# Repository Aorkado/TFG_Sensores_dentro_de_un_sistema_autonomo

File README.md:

# Sensores dentro de un sistema autónomo

En este repositorio se recoge el software desarrollado y las placas diseñadas. Varios ejemplos quedan por desarrollar o explicar debidamente. El proyecto aún está en progreso.

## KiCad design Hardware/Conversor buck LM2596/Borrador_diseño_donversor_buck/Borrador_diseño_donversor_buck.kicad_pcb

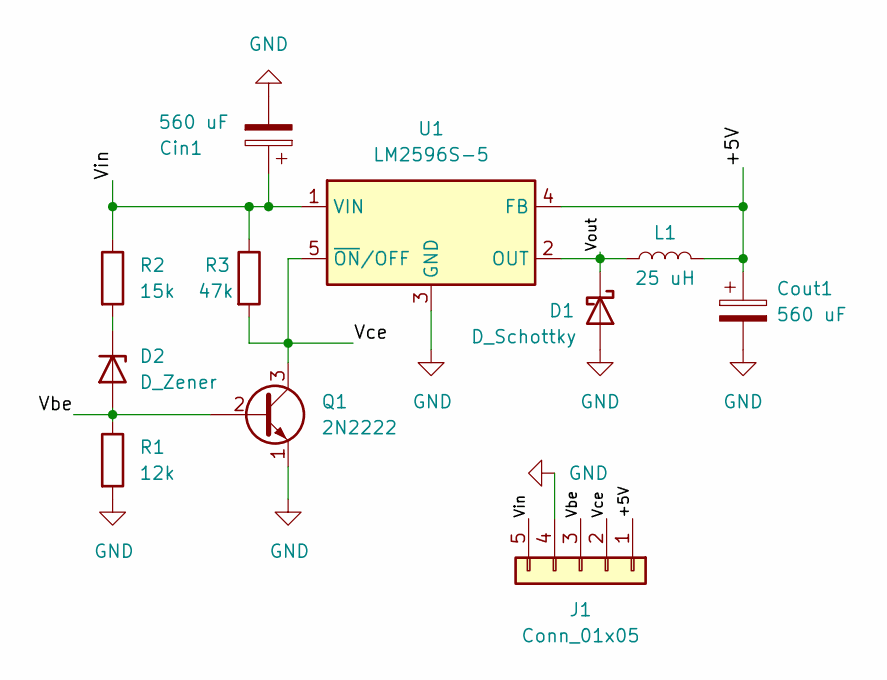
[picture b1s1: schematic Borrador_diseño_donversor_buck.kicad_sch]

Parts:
Cin1: 560 uF; CP_Radial_D8.0mm_P3.80mm
Cout1: 560 uF; CP_Radial_D8.0mm_P3.80mm
D1: D_Schottky; D_DO-201AD_P15.24mm_Horizontal
D2: D_Zener; D_A-405_P12.70mm_Horizontal
J1: Conn_01x05; PinHeader_1x05_P2.54mm_Vertical
L1: 25 uH; PE-54041
Q1: 2N2222; TO-39-3
R1: 12k; R_0805_2012Metric
R2: 15k; R_0805_2012Metric
R3: 47k; R_0603_1608Metric
U1: LM2596S-5; TO-263-5_TabPin3

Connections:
/+5V: Cout1.1, J1.1, L1.2, U1.4 (FB)
/Vbe: D2.2 (A), J1.3, Q1.2 (B), R1.1
/Vce: J1.2, Q1.3 (C), R3.2, U1.5 (~ON/OFF)
/Vin: Cin1.1, J1.5, R2.1, R3.1, U1.1 (VIN)
/Vout: D1.1 (K), L1.1, U1.2 (OUT)
GND: Cin1.2, Cout1.2, D1.2 (A), J1.4, Q1.1 (E), R1.2, U1.3 (GND)
unnamed: D2.1 (K), R2.2

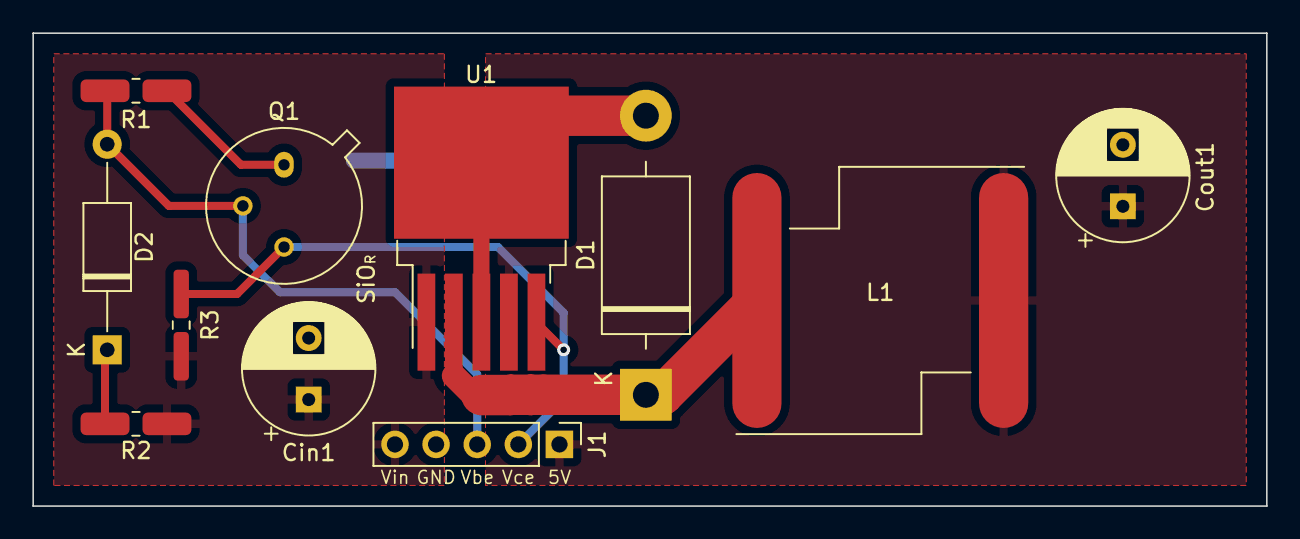
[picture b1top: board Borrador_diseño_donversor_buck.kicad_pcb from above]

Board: 2 copper layers, 76.2 x 29.2 mm, 11 parts (0 on the bottom side), 7 nets.

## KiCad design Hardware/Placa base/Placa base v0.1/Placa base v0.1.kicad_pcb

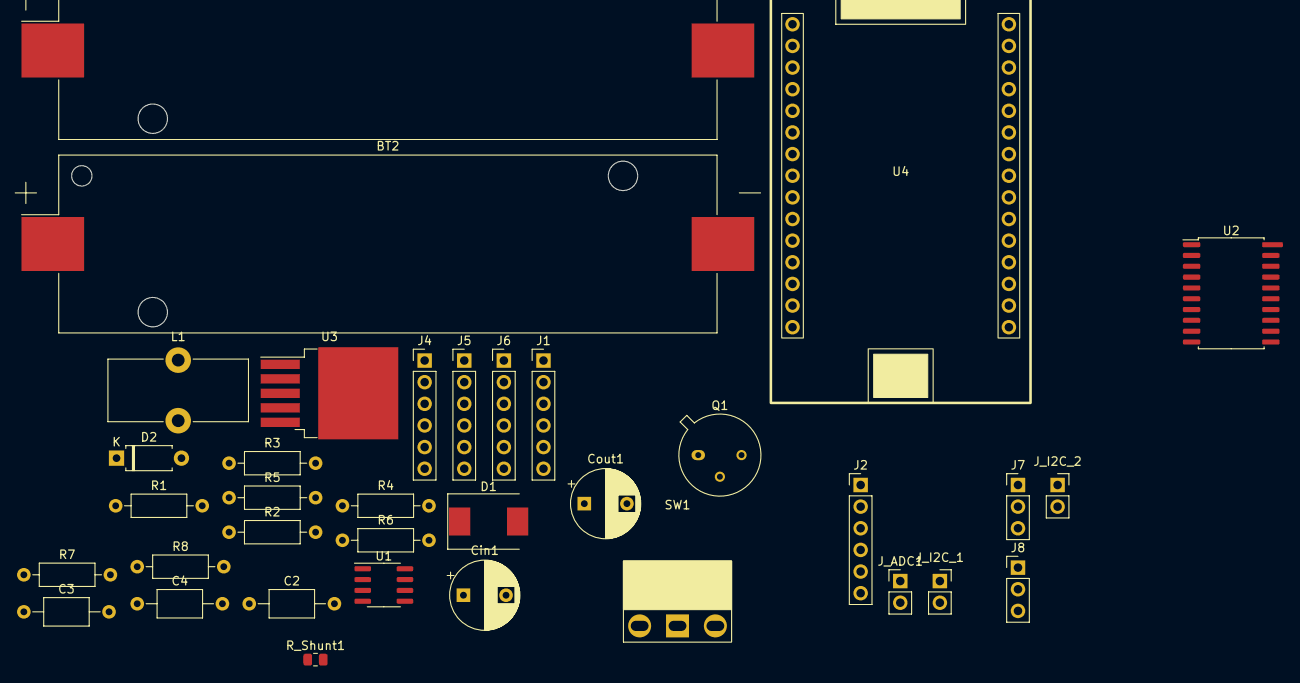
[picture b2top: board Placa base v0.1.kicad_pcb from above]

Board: 2 copper layers, 35 parts (0 on the bottom side), 34 nets, no tracks yet.

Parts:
BT1, BT2: Battery_Cell; BatteryHolder_Keystone_1042_1x18650
C2, C3: 10 nF; C_Axial_L5.1mm_D3.1mm_P10.00mm_Horizontal
C4: 100 nF; C_Axial_L5.1mm_D3.1mm_P10.00mm_Horizontal
Cin1: 560 uF; CP_Radial_D8.0mm_P5.00mm
Cout1: 560 uF; CP_Radial_D8.0mm_P5.00mm
D1: D_Schottky; D_SMC
D2: D_Zener; D_A-405_P7.62mm_Horizontal
J1: Motor_Right; PinHeader_1x06_P2.54mm_Vertical
J2: Motor_Left; PinHeader_1x06_P2.54mm_Vertical
J4: Left_VL53L0X; PinHeader_1x06_P2.54mm_Vertical
J5: Center_VL53L0X; PinHeader_1x06_P2.54mm_Vertical
J6: Right_VL53L0X; PinHeader_1x06_P2.54mm_Vertical
J7, J8: Conn_01x03; PinHeader_1x03_P2.54mm_Vertical
J_ADC1: Conn_01x02; PinHeader_1x02_P2.54mm_Vertical
J_I2C_1, J_I2C_2: Conn_01x02; PinSocket_1x02_P2.54mm_Vertical
L1: 25 uH; L_Toroid_Vertical_L16.3mm_W7.1mm_P7.11mm_Pulse_H
Q1: 2N2219; TO-39-3
R1, R2, R7, R8: 10k; R_Axial_DIN0207_L6.3mm_D2.5mm_P10.16mm_Horizontal
R3: 47k; R_Axial_DIN0207_L6.3mm_D2.5mm_P10.16mm_Horizontal
R4, R5, R6: 1.8k; R_Axial_DIN0207_L6.3mm_D2.5mm_P10.16mm_Horizontal
R_Shunt1: 0.075 Ohm; R_0805_2012Metric
SW1: SW_DPDT_x2; SPDT Switch
U1: INA270; SOIC-8_3.9x4.9mm_P1.27mm
U2: L293DD; SOIC-20W_7.5x12.8mm_P1.27mm
U3: LM2596S-5; TO-263-5_TabPin3
U4: Esp32-DevKit-V1; ESP32 DevKit-V1

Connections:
+3V3: J4.1, J5.1, J6.1, J8.1, J8.2, J8.3, R4.1, R5.1, R6.1, R7.2, R8.2, U4.16 (3V3)
+5V: C2.2, Cout1.1, J1.5, J2.2, J7.1, J7.2, J7.3, L1.2, U1.6 (V+), U2.10 (VS), U2.20 (VSS), U3.4 (FB), U4.15 (VIN)
+BATT: BT1.1 (+), SW1.2 (B)
/ADC: J_ADC1.2, U4.19 (D2/CS)
/ADC_GPIO: J_ADC1.1, U4.20 (D4)
/BATTERY_CURRENT: U1.5, U4.6 (D32)
/ENC_LEFT_A: J2.3, U4.3 (VN)
/ENC_LEFT_B: J2.4, U4.2 (VP)
/ENC_RIGHT_A: J1.4, U4.4 (D34)
/ENC_RIGHT_B: J1.3, U4.5 (D35)
/M_LEFT+: J2.1, U2.13 (OUTPUT3)
/M_LEFT-: J2.6, U2.18 (OUTPUT4)
/M_LEFT_DIR1: U2.12 (INPUT3), U4.13 (D13)
/M_LEFT_DIR2: U2.19 (INPUT4), U4.11 (D14)
/M_RIGHT+: J1.6, U2.3 (OUTPUT1)
/M_RIGHT-: J1.1, U2.8 (OUTPUT2)
/M_RIGHT_DIR1: U2.2 (INPUT1), U4.24 (D18/SCK)
/M_RIGHT_DIR2: U2.9 (INPUT2), U4.25 (D19/MISO)
/PWM_LEFT: U2.11 (ENABLE2), U4.7 (D33)
/PWM_RIGHT: U2.1 (ENABLE1), U4.30 (D23/MOSI)
/SCL: J4.4, J5.4, J6.4, J_I2C_1.1, J_I2C_2.1, R8.1, U4.29 (D22/SCL)
/SDA: J4.3, J5.3, J6.3, J_I2C_1.2, J_I2C_2.2, R7.1, U4.26 (D21/SDA)
/XSHUT_C: J5.5, R5.2, U4.9 (D26)
/XSHUT_L: J4.5, R6.2, U4.8 (D25)
/XSHUT_R: J6.5, R4.2, U4.10 (D27)
GND: BT2.2 (-), C2.1, C3.2, C4.2, Cin1.2, Cout1.2, D1.2 (A), J1.2, J2.5, J4.6, J5.6, J6.6, Q1.1 (E), R1.2, U1.2 (GND), U1.7 (NC), U2.4 (GND), U2.5 (GND), U2.6 (GND), U2.7 (GND), U2.14 (GND), U2.15 (GND), U2.16 (GND), U2.17 (GND), U3.3 (GND), U4.14 (GND), U4.17 (GND)
unnamed: BT1.2 (-), BT2.1 (+)
unnamed: C3.1, C4.1, U1.3 (PRE_OUT), U1.4 (BUF_IN)
unnamed: D1.1 (K), L1.1, U3.2 (OUT)
unnamed: D2.1 (K), R2.2
unnamed: D2.2 (A), Q1.2 (B), R1.1
unnamed: Q1.3 (C), R3.2, U3.5 (~ON/OFF)
VCC: R_Shunt1.1, SW1.3 (C), U1.8 (IN+)
VDC: Cin1.1, R2.1, R3.1, R_Shunt1.2, U1.1 (IN-), U3.1 (VIN)

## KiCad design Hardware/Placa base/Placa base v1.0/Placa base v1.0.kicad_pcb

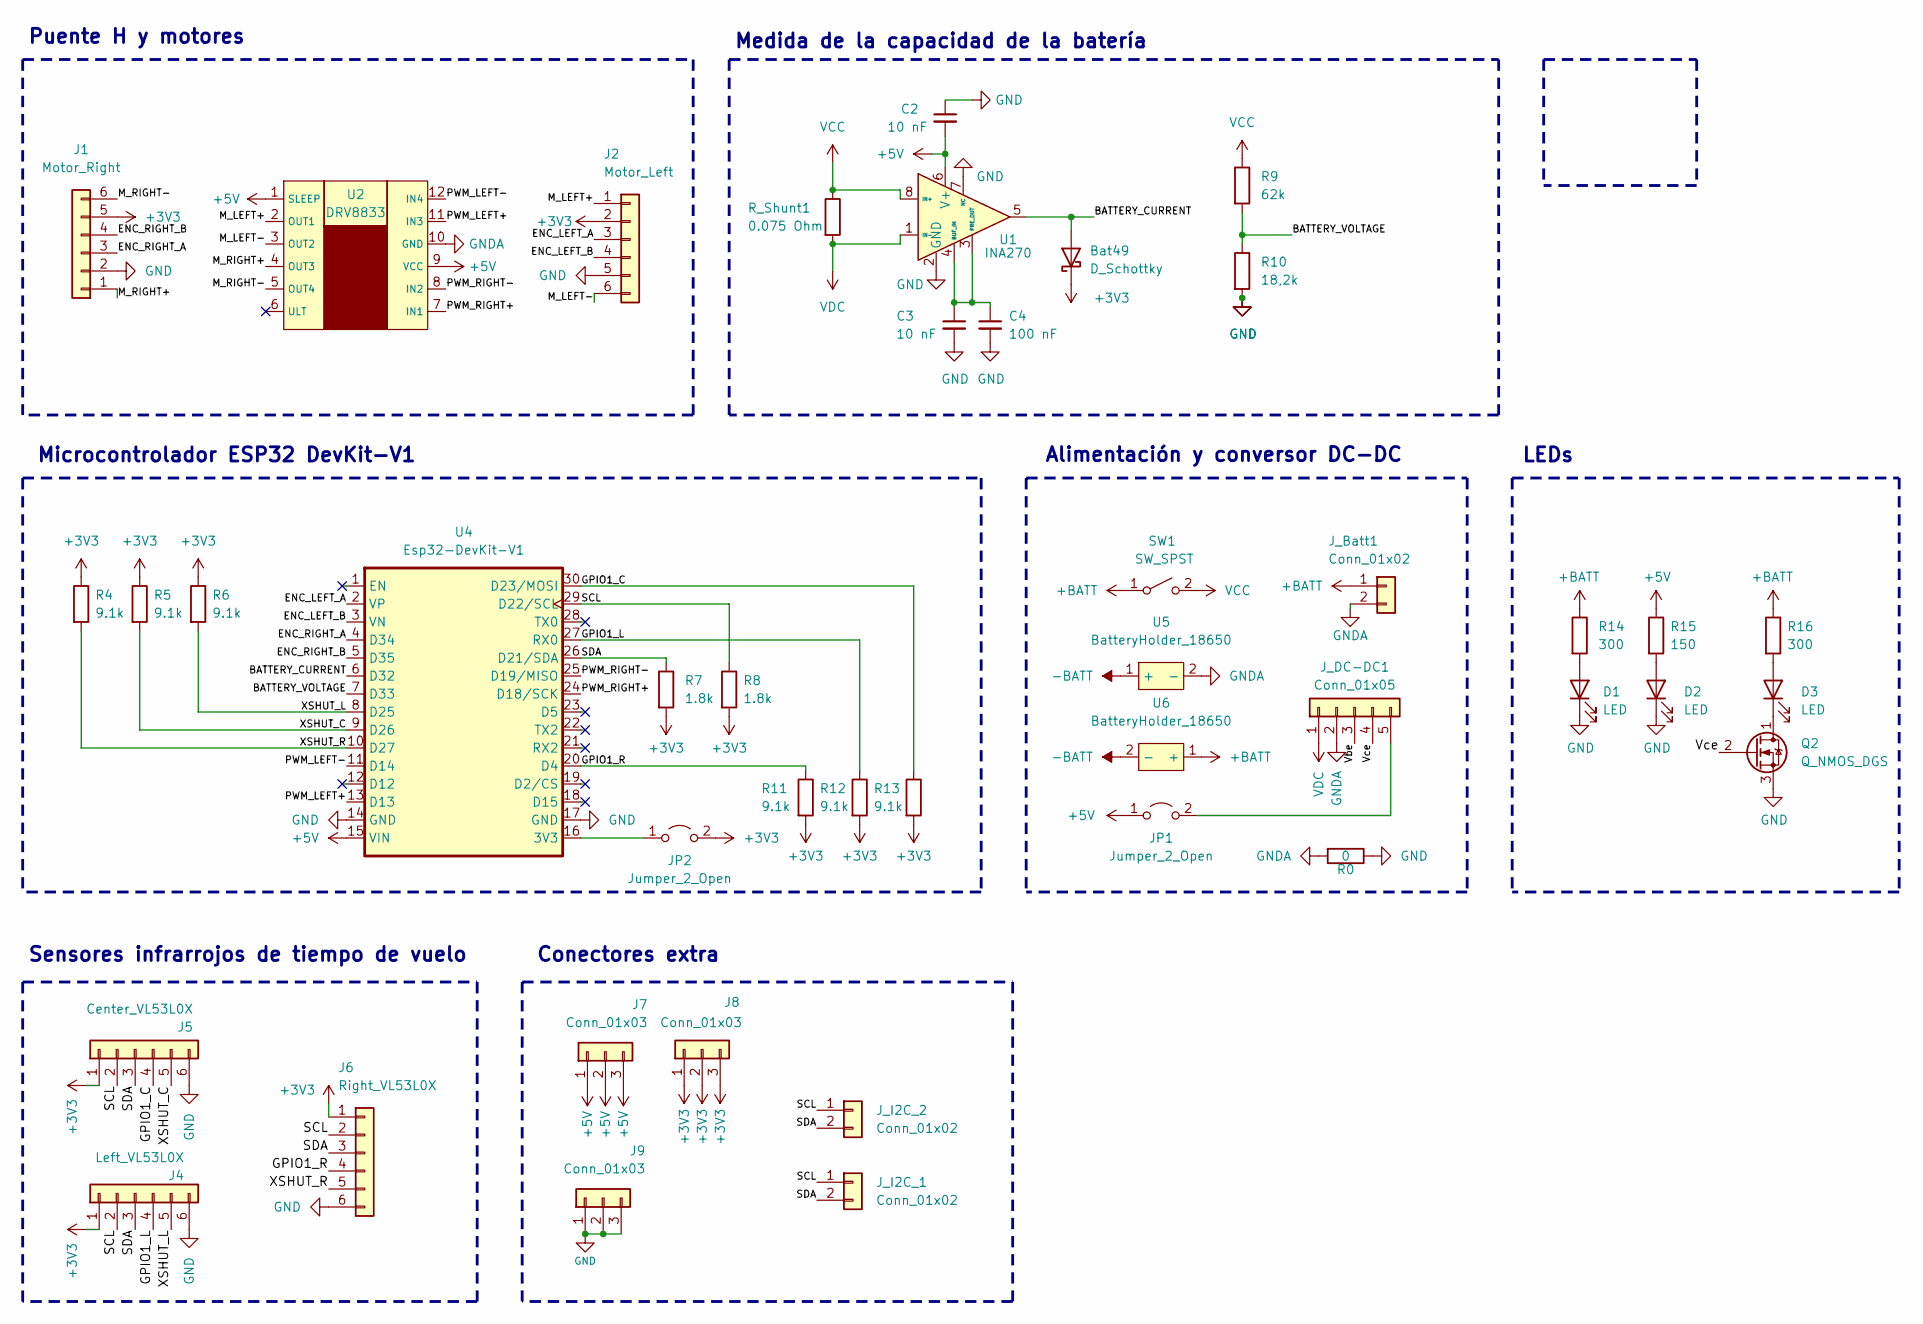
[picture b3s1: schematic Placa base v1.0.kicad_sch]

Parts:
Bat49: D_Schottky; D_5W_P12.70mm_Horizontal
C2, C3: 10 nF; C_Axial_L5.1mm_D3.1mm_P7.50mm_Horizontal
C4: 100 nF; C_Axial_L5.1mm_D3.1mm_P7.50mm_Horizontal
D1, D2, D3: LED; LED_D3.0mm
J1: Motor_Right; PinHeader_1x06_P2.54mm_Vertical
J2: Motor_Left; PinHeader_1x06_P2.54mm_Vertical
J4: Left_VL53L0X; PinHeader_1x06_P2.54mm_Vertical
J5: Center_VL53L0X; PinHeader_1x06_P2.54mm_Vertical
J6: Right_VL53L0X; PinHeader_1x06_P2.54mm_Vertical
J7, J8, J9: Conn_01x03; PinHeader_1x03_P2.54mm_Vertical
JP1, JP2: Jumper_2_Open; TestPoint_2Pads_Pitch2.54mm_Drill0.8mm
J_Batt1: Conn_01x02; PinHeader_1x02_P2.54mm_Vertical
J_DC-DC1: Conn_01x05; PinHeader_1x05_P2.54mm_Vertical
J_I2C_1, J_I2C_2: Conn_01x02; PinSocket_1x02_P2.54mm_Vertical
Q2: Q_NMOS_DGS; TO-92L_Inline_Wide
R0: 0; R_Axial_DIN0204_L3.6mm_D1.6mm_P5.08mm_Vertical
R4, R5, R6, R11, R12, R13: 9.1k; R_0805_2012Metric_Pad1.20x1.40mm_HandSolder
R7, R8: 1.8k; R_1206_3216Metric
R9: 62k; R_0805_2012Metric_Pad1.20x1.40mm_HandSolder
R10: 18,2k; R_0805_2012Metric_Pad1.20x1.40mm_HandSolder
R14, R16: 300; R_0805_2012Metric
R15: 150; R_1206_3216Metric
R_Shunt1: 0.075 Ohm; R_0805_2012Metric
SW1: SW_SPST; SPDT Switch
U1: INA270; SOIC-8_3.9x4.9mm_P1.27mm
U2: DRV8833
U4: Esp32-DevKit-V1; ESP32 DevKit-V1
U5, U6: BatteryHolder_18650

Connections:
+3V3: Bat49.1 (K), J1.5, J2.2, J4.1, J5.1, J6.1, J8.1, J8.2, J8.3, JP2.2 (B), R4.1, R5.1, R6.1, R7.2, R8.2, R11.2, R12.2, R13.2
+5V: C2.2, J7.1, J7.2, J7.3, JP1.1 (A), R15.1, U1.6 (V+), U2.1 (SLEEP), U2.9 (VCC), U4.15 (VIN)
+BATT: J_Batt1.1, R14.1, R16.1, SW1.1 (A), U6.1 (+)
-BATT: U5.1 (+), U6.2 (-)
/BATTERY_CURRENT: Bat49.2 (A), U1.5, U4.6 (D32)
/BATTERY_VOLTAGE: R9.2, R10.1, U4.7 (D33)
/ENC_LEFT_A: J2.3, U4.2 (VP)
/ENC_LEFT_B: J2.4, U4.3 (VN)
/ENC_RIGHT_A: J1.3, U4.4 (D34)
/ENC_RIGHT_B: J1.4, U4.5 (D35)
/GPIO1_C: J5.4, R13.1, U4.30 (D23/MOSI)
/GPIO1_L: J4.4, R12.1, U4.27 (RX0)
/GPIO1_R: J6.4, R11.1, U4.20 (D4)
/M_LEFT+: J2.1, U2.2 (OUT1)
/M_LEFT-: J2.6, U2.3 (OUT2)
/M_RIGHT+: J1.1, U2.4 (OUT3)
/M_RIGHT-: J1.6, U2.5 (OUT4)
/PWM_LEFT+: U2.11 (IN3), U4.13 (D13)
/PWM_LEFT-: U2.12 (IN4), U4.11 (D14)
/PWM_RIGHT+: U2.7 (IN1), U4.24 (D18/SCK)
/PWM_RIGHT-: U2.8 (IN2), U4.25 (D19/MISO)
/SCL: J4.2, J5.2, J6.2, J_I2C_1.1, J_I2C_2.1, R8.1, U4.29 (D22/SCL)
/SDA: J4.3, J5.3, J6.3, J_I2C_1.2, J_I2C_2.2, R7.1, U4.26 (D21/SDA)
/Vbe: J_DC-DC1.3
/Vce: J_DC-DC1.4, Q2.2 (G)
/XSHUT_C: J5.5, R5.2, U4.9 (D26)
/XSHUT_L: J4.5, R6.2, U4.8 (D25)
/XSHUT_R: J6.5, R4.2, U4.10 (D27)
GND: C2.1, C3.2, C4.2, D1.1 (K), D2.1 (K), J1.2, J2.5, J4.6, J5.6, J6.6, J9.1, J9.2, J9.3, Q2.3 (S), R0.1, R10.2, U1.2 (GND), U1.7 (NC), U4.14 (GND), U4.17 (GND)
GNDA: J_Batt1.2, J_DC-DC1.2, R0.2, U2.10 (GND), U5.2 (-)
unnamed: C3.1, C4.1, U1.3 (PRE_OUT), U1.4 (BUF_IN)
unnamed: D1.2 (A), R14.2
unnamed: D2.2 (A), R15.2
unnamed: D3.1 (K), Q2.1 (D)
unnamed: D3.2 (A), R16.2
unnamed: JP1.2 (B), J_DC-DC1.5
unnamed: JP2.1 (A), U4.16 (3V3)
VCC: R9.1, R_Shunt1.1, SW1.2 (B), U1.8 (IN+)
VDC: J_DC-DC1.1, R_Shunt1.2, U1.1 (IN-)

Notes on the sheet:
Microcontrolador ESP32 DevKit-V1
Conectores extra
Sensores infrarrojos de tiempo de vuelo
Medida de la capacidad de la batería
Alimentación y conversor DC-DC
Puente H y motores
LEDs

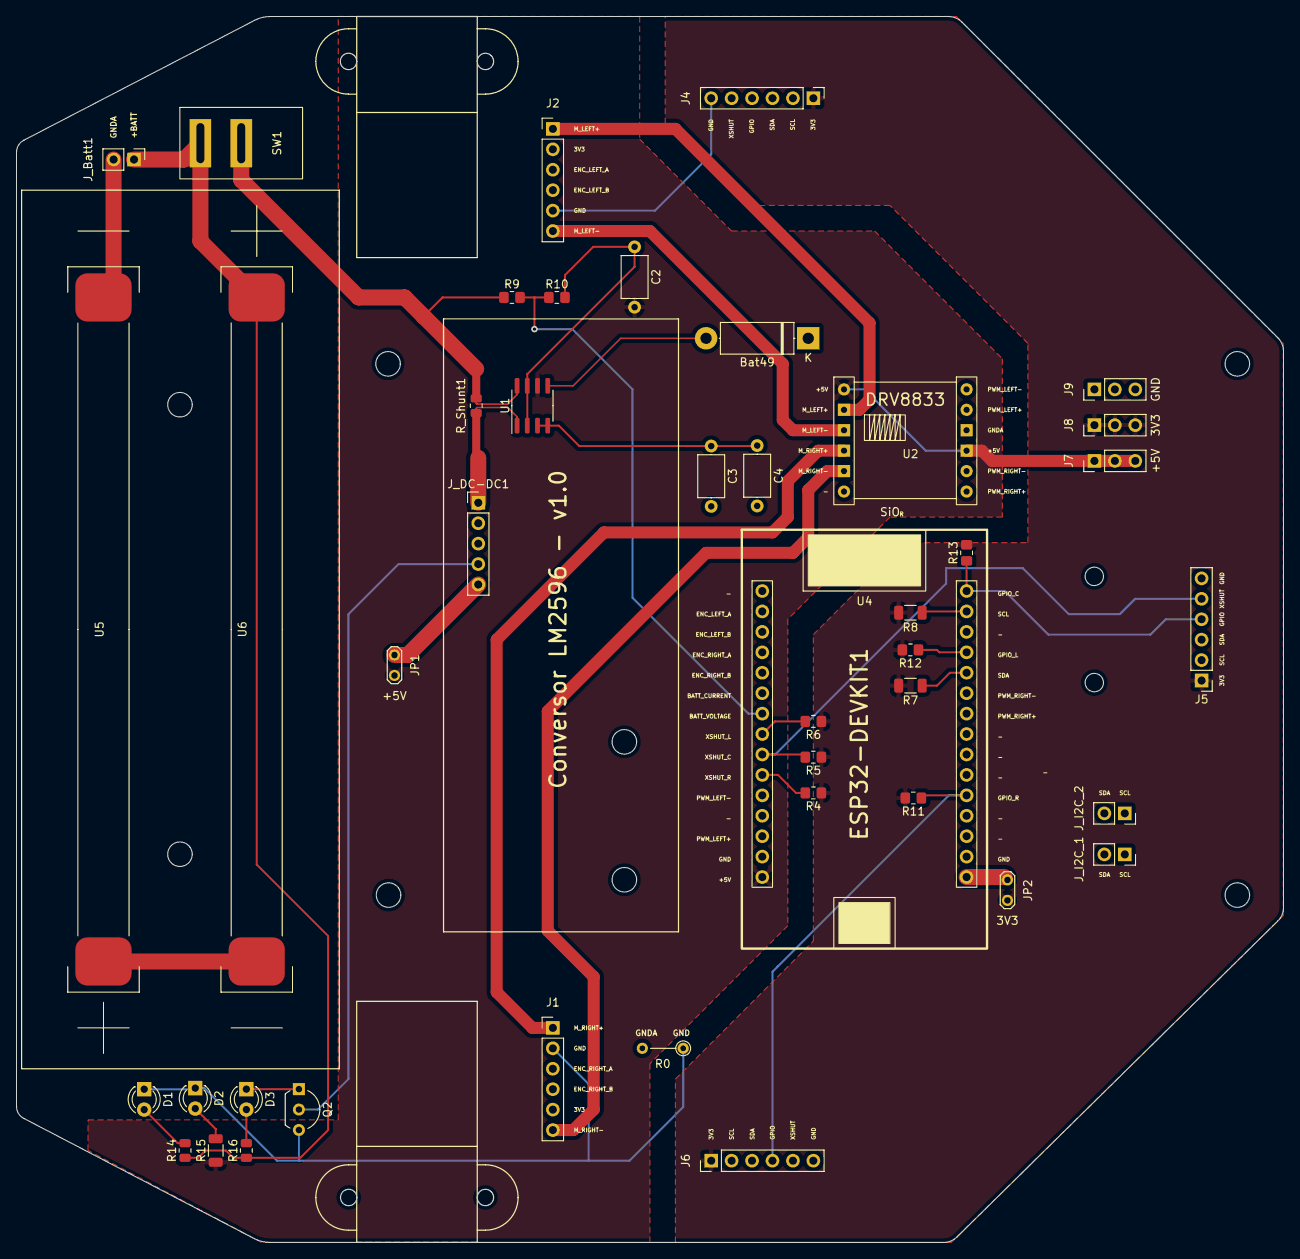
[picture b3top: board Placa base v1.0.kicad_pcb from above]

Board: 4 copper layers, 157.5 x 152.4 mm, 43 parts (0 on the bottom side), 38 nets.

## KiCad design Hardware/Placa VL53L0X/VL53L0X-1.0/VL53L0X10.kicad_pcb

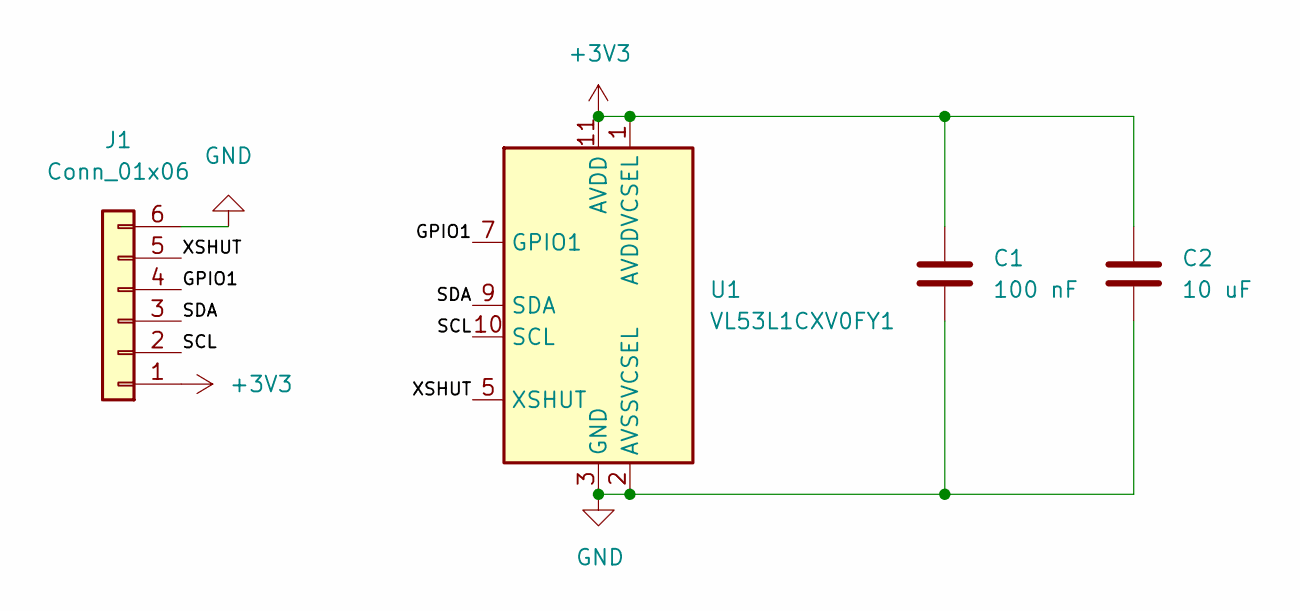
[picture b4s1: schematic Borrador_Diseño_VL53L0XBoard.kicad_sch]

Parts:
C1: 100 nF; C_1206_3216Metric_Pad1.33x1.80mm_HandSolder
C2: 10 uF; C_1206_3216Metric_Pad1.33x1.80mm_HandSolder
J1: Conn_01x06; PinHeader_1x06_P2.54mm_Vertical
U1: VL53L1CXV0FY1; ST_VL53L1x

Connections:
+3V3: C1.2, C2.2, J1.1, U1.1 (AVDDVCSEL), U1.11 (AVDD)
/GPIO1: J1.4, U1.7 (GPIO1)
/SCL: J1.2, U1.10 (SCL)
/SDA: J1.3, U1.9 (SDA)
/XSHUT: J1.5, U1.5 (XSHUT)
GND: C1.1, C2.1, J1.6, U1.2 (AVSSVCSEL), U1.3 (GND), U1.4 (GND), U1.6 (GND), U1.12 (GND)

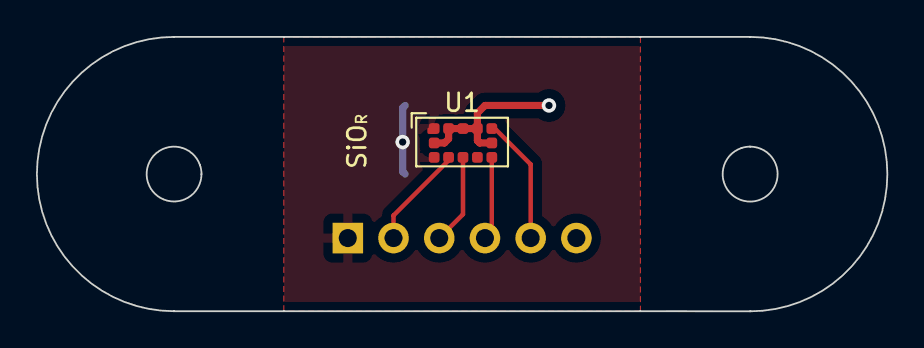
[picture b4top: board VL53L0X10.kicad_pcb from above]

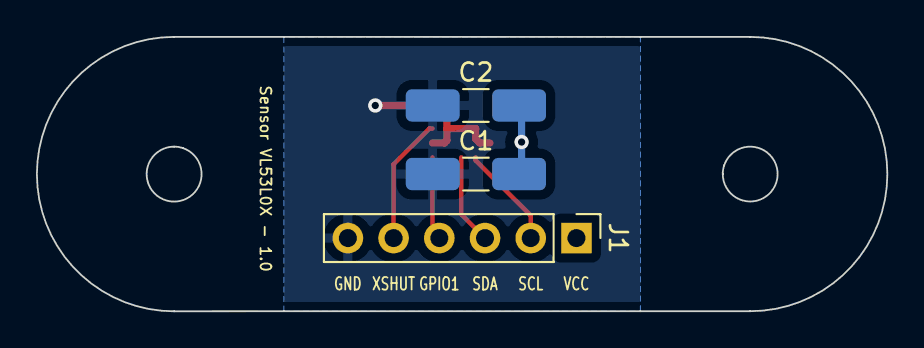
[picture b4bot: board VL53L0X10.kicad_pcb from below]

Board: 2 copper layers, 47.2 x 15.2 mm, 4 parts (3 on the bottom side), 6 nets.

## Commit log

2025-05-27 Creadas carpetas Software y Hardware
2025-05-27 Added README.md
2025-05-27 Removed Software/
2025-05-27 Added software directory
2025-05-27 Added directory of PWM tests
2025-05-27 Added PWM tests
